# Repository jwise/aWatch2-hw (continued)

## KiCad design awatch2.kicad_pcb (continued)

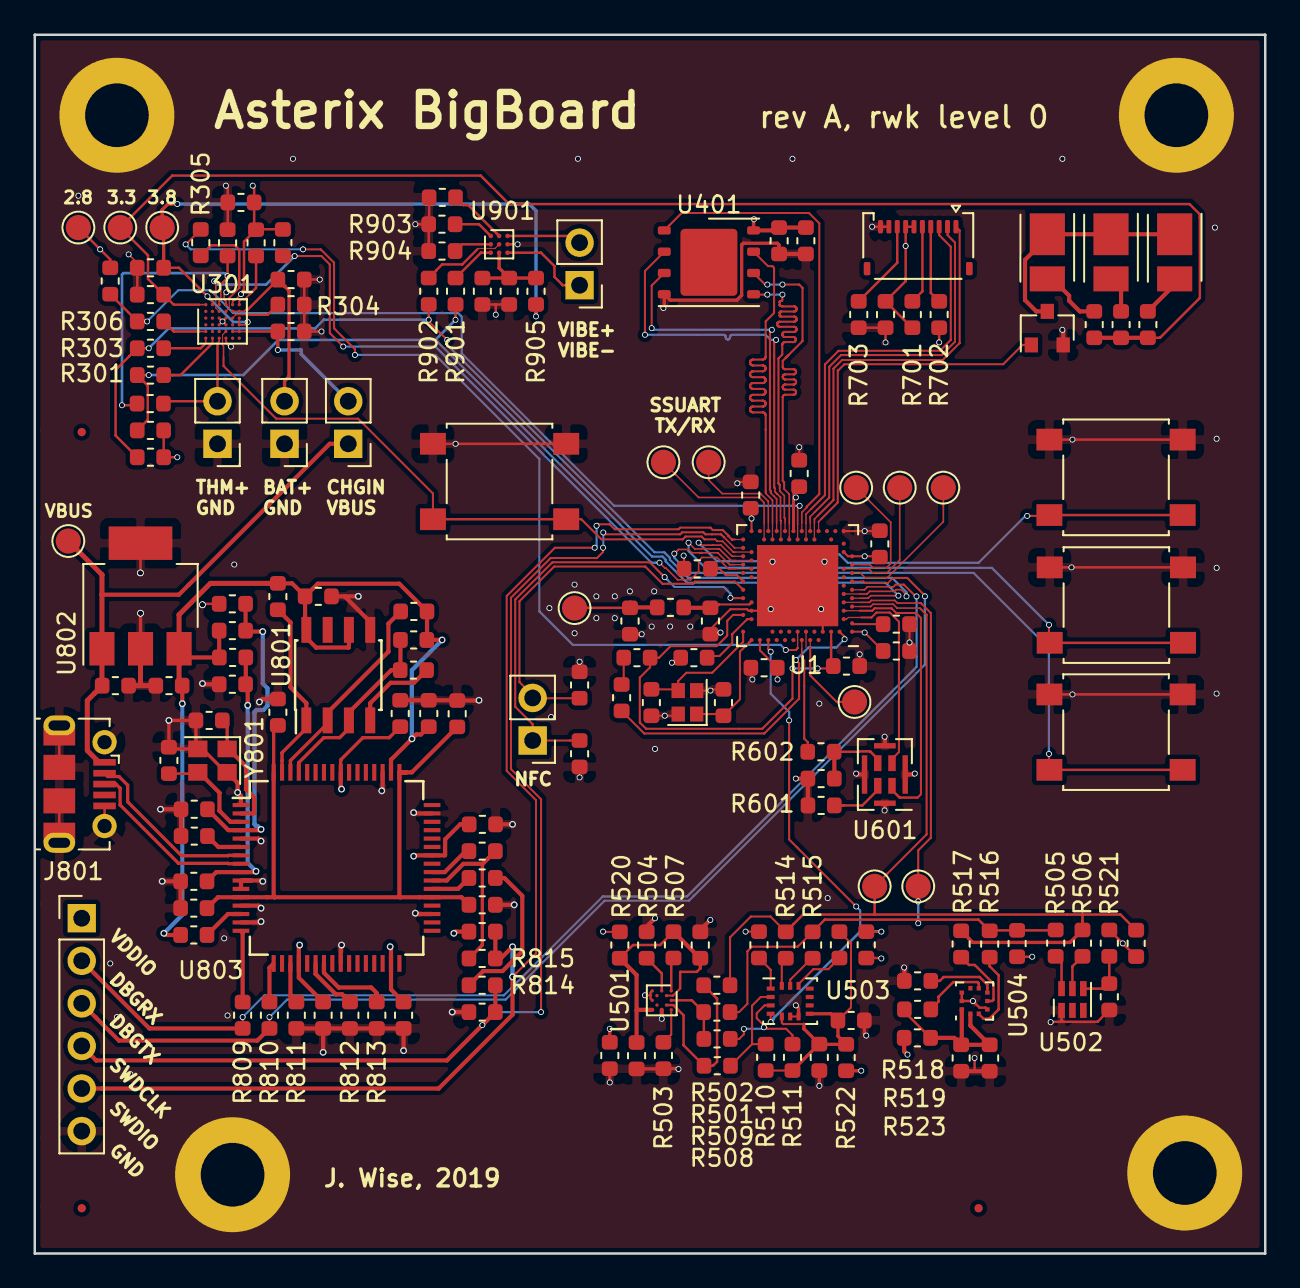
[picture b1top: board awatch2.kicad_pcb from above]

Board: 4 copper layers, 73.4 x 72.7 mm, 177 parts (1 on the bottom side), 123 nets.

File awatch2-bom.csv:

Reference, Quantity, Value, Footprint, Datasheet, DigiKey PN
C1 C2 ,2,"10pF NP0","Capacitor_SMD:C_0603_1608Metric","~","311-3869-1-ND"
C11 ,1,"100pF NP0","Capacitor_SMD:C_0603_1608Metric","~","311-1069-1-ND"
C14 C15 C301 C302 C303 C306 C401 C501 C504 C701 C901 C903 ,12,"1.0µF X7R","Capacitor_SMD:C_0603_1608Metric","~","1276-1946-1-ND"
C201 C202 ,2,"?pF NP0","Capacitor_SMD:C_0603_1608Metric","~"
C3 C4 ,2,"1.0pF NP0","Capacitor_SMD:C_0603_1608Metric","~","1276-1293-1-ND"
C304 C305 ,2,"10µF X5R","Capacitor_SMD:C_0603_1608Metric","~","490-12538-1-ND"
C12 C402 C5 C502 C503 C505 C506 C507 C508 C601 C7 C8 C801 C802 C803 C809 C810 C811 C812 C813 C814 C815 C816 C817 C818 C902 ,26,"0.1µF X7R","Capacitor_SMD:C_0603_1608Metric","~","1276-1061-1-ND"
C6 C804 C806 C808 ,4,"4.7µF X7R","Capacitor_SMD:C_0603_1608Metric","~","1276-2087-1-ND"
C805 C807 ,2,"22pF NP0","Capacitor_SMD:C_0603_1608Metric","~","399-7874-1-ND"
C9 ,1,"820pF NP0","Capacitor_SMD:C_0603_1608Metric","~","311-3959-1-ND"
D701 D702 D703 ,3,"SPMWHT541ML5XATMS0","LED_SMD:LED_PLCC_2835_Handsoldering","~","1510-1284-1-ND"
G1 ,1,"Logo","awatch2-footprints:littlehatguy","~"
H1001 H1002 H1003 H1004 ,4,"6-32","awatch2-footprints:6-32","~"
H1005 H1006 H1007 ,3,"Fiducial","Fiducial:Fiducial_0.5mm_Dia_1mm_Outer","~"
J101 J102 J103 J104 J301 ,5,"Conn_01x02","Connector_PinHeader_2.54mm:PinHeader_1x02_P2.54mm_Vertical","~","S1011EC-02-ND"
Jxxx,1,,,,S9341-ND
J801 ,1,"Molex 1050170001","Connector_USB:USB_Micro-B_Molex-105017-0001","~","WM1399CT-ND"
J802 ,1,"Conn_01x06","Connector_PinHeader_2.54mm:PinHeader_1x06_P2.54mm_Vertical","~","S1011EC-06-ND"
L1 ,1,"3.8nH","Inductor_SMD:L_0603_1608Metric","~","712-1429-1-ND"
L2 ,1,"10µH","Inductor_SMD:L_0603_1608Metric","~","445-6755-1-ND"
L3 ,1,"15nH","Inductor_SMD:L_0603_1608Metric","~","CI160808-15NJCT-ND"
L301 ,1,"2.2µH","Inductor_SMD:L_0603_1608Metric","~","445-6385-1-ND"
L801 L802 ,2,"bead","Inductor_SMD:L_0603_1608Metric","~","587-1926-1-ND"
Q701 ,1,"FDV301N","Package_TO_SOT_SMD:SOT-23","https://www.fairchildsemi.com/datasheets/2N/2N7002.pdf","FDV301NCT-ND"
R1 R2 R3 R4 R510 R511 R802 R806 ,8,"2.2k","Resistor_SMD:R_0603_1608Metric","~","MCT0603-2.20K-CFCT-ND"
R201 R302 R307 R801 R803 R804 R816 R817 ,8,"10k","Resistor_SMD:R_0603_1608Metric","~","MCT0603-10.0K-CFCT-ND"
R202 R501 R502 ,3,"n/c","Resistor_SMD:R_0603_1608Metric","~"
R304 ,1,"12.4k","Resistor_SMD:R_0603_1608Metric","~","RNCP0603FTD12K4CT-ND"
R301 R303 R305 R306 R503 R504 R505 R506 R507 R508 R509 R512 R513 R514 R515 R516 R517 R518 R519 R520 R521 R522 R523 R601 R602 R701 R702 R703 R809 R810 R811 R812 R813 R814 R815 R901 R902 R903 R904 R905 ,40,"0","Resistor_SMD:R_0603_1608Metric","~","MCT0603-0.0-ZZCT-ND"
R704 R705 R706 R808 ,4,"160","Resistor_SMD:R_0603_1608Metric","~","749-1765-1-ND"
R805 ,1,"12k 1%","Resistor_SMD:R_0603_1608Metric","~","MCT0603-12.0K-CFCT-ND"
R807 ,1,"470","Resistor_SMD:R_0603_1608Metric","~","MCT0603-470-CFCT-ND"
SW101 SW102 SW103 SW104 ,4,"B3S-1000","Button_Switch_SMD:SW_SPST_B3S-1000","","SW836CT-ND"
TP101 TP102 TP103 TP104 TP105 TP106 TP107 TP108 TP109 TP301 TP302 TP303 TP801 ,13,"TestPoint","TestPoint:TestPoint_Pad_D1.5mm","~"
U1 ,1,"nRF52840","Package_DFN_QFN:Nordic_AQFN-73-1EP_7x7mm_P0.5mm","http://infocenter.nordicsemi.com/topic/com.nordic.infocenter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","1490-1071-1-ND"
U301 ,1,"MAX14690A","awatch2-footprints:WLP-36_2.69x2.44mm_Layout6x6_P0.4mm_Ball0.22mm_Pad0.2mm_NSMD","","MAX14745FEWX+-ND see pmic-options.txt"
U401 ,1,"W25Q128JVPIQTR","Package_SON:WSON-8-1EP_6x5mm_P1.27mm_EP3.4x4mm","","W25Q128JVPIQCT-ND"
U501 ,1,"BMM150","awatch2-footprints:WLCSP-12_1.56x1.56mm_Layout5x5_P0.283mm_Ball0.25mm_Pad0.2mm_NSMD","","828-1044-1-ND"
U502 ,1,"APDS-9306-065","awatch2-footprints:DFN-6_2x2mm_P0.53mm","","516-3578-1-ND"
U503 ,1,"BMI160","awatch2-footprints:BMI160","","828-1057-1-ND"
U504 ,1,"BMP388","awatch2-footprints:BMP388","","828-1079-1-ND"
U601 ,1,"SPK0641HT4H-1","awatch2-footprints:SPK0641HT4H","","423-1425-1-ND"
U701 ,1,"AYF531035 (LS013B7DH05)","awatch2-footprints:Panasonic_Y5B_AYF531035_1x10-1MP_P0.50mm_Horizontal","","255-5667-ND, Adafruit display"
U801 ,1,"AT93C46DN-SH-T","Package_SO:SOIC-8_3.9x4.9mm_P1.27mm","http://ww1.microchip.com/downloads/en/DeviceDoc/20001749K.pdf","AT93C46DN-SH-TCT-ND"
U802 ,1,"MCP1703A-3302_SOT223","Package_TO_SOT_SMD:SOT-223-3_TabPin2","http://ww1.microchip.com/downloads/en/DeviceDoc/20005122B.pdf","MCP1703AT-3302E/DBCT-ND"
U803 ,1,"FT2232HL","Package_QFP:LQFP-64_10x10mm_P0.5mm","http://www.ftdichip.com/Products/ICs/FT2232H.html","768-1024-1-ND"
U901 ,1,"DRV2604","awatch2-footprints:Texas_DSBGA-9_1.47x1.47mm_Layout3x3_P0.5mm_NSMD","","296-45407-1-ND"
X1 ,1,"ABM11W-32.0000MHZ-8-B1U-T3","Crystal:Crystal_SMD_2016-4Pin_2.0x1.6mm","~","535-13899-1-ND"
Y801 ,1,"FH1200004","Crystal:Crystal_SMD_2520-4Pin_2.5x2.0mm","~","FH1200004CT-ND"
,4,hex standoff 6-32 1/2",,,36-1451C-ND
,4,pan screw 6-32 3/8",,,36-9904-ND

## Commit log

2018-12-30 aWatch2: initial import with nRF, PMIC, and Flash
2018-12-30 add current design notes
2018-12-30 add sensors
2018-12-30 add mic
2018-12-30 Add display. Add +3.3V LDO for backlight.
2018-12-30 backlight PWM through a FET
2018-12-30 add FTDI
2018-12-30 add vibrate
2018-12-30 annotate all
2018-12-30 add power measurement cuts
2018-12-30 update xtal caps on FTDI
2019-01-02 Add footprints.
2019-01-02 add BOM part for connector for display
2019-01-02 add ground pin for DRV2604
2019-01-03 FTDI placement
2019-01-03 Route FTDI.
2019-01-04 PMIC relative placement and routing
2019-01-04 place and route ambient light sensor
2019-01-04 Place and route pressure sensor.
2019-01-04 IMU and magnetometer placed and routed
2019-01-04 placed and routed all four sensors
2019-01-06 vibe, mic, display P&R
2019-01-06 relative placement and routing for nRF52840
2019-01-06 place PMIC and vibrate driver
2019-01-06 place PMIC I2C pullups
2019-01-11 Pseudofinal placement.
2019-01-13 route NFC
2019-01-15 nRF pinout changes for routability
2019-01-15 some PMIC and sensor routing
2019-01-16 fully routed
2019-01-16 passes DRC; top and bottom ground planes added
2019-01-16 update solder mask clearance for oshpark
2019-01-17 mounting holes, fiducials
2019-01-17 oops, connect the rest of the grounds
2019-01-19 approx. final layout
2019-01-20 BOM fully populated
2019-01-20 update values in pcb
2019-01-27 Add BOMs
2019-03-03 add TODO from first weekend
2019-03-03 bringup status update from tonight
2019-03-04 latest bringup status update
2019-03-18 board checkout update
2019-03-18 a few more updates
